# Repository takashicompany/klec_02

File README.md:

# KLEC-02 "Gravity-36"

https://x.com/Hottyhottea/status/1843859533871058982

# 部品リスト

|画像|部品名|個数|備考|
|:--|:--|:--|:--|
||KLEC-02 PCB|1||
||[Pro Micro](https://shop.yushakobo.jp/products/21)|2|どれを買っていいか分からない場合は[コンスルー付きのセット](https://shop.yushakobo.jp/products/21)の購入を推奨します。|
||[タクトスイッチ](https://shop.yushakobo.jp/products/a0800ts-01-1)|2||
||[コンスルー](https://shop.yushakobo.jp/products/31)|4|PCBとPro Microを接続する端子です。Pro Microに付属するピンヘッダでの取り付けも可能ですが、作業ミスや故障した際の取り替えが容易になりますので、**コンスルーの使用を強く推奨します。ピンヘッダでの取り付けは当キーボードと当ビルドガイドではサポートしません。** コンスルーの必要な高さはPro Microによって異なりますので、販売元にご確認ください。コンスルーについての詳細な説明は[こちら](https://scrapbox.io/self-made-kbds-ja/%E3%82%B3%E3%83%B3%E3%82%B9%E3%83%AB%E3%83%BC)をご一読ください。併せて[取り付け方の説明](https://yushakobo.zendesk.com/hc/ja/articles/360044233974-%E3%82%B3%E3%83%B3%E3%82%B9%E3%83%AB%E3%83%BC-%E3%82%B9%E3%83%97%E3%83%AA%E3%83%B3%E3%82%B0%E3%83%94%E3%83%B3%E3%83%98%E3%83%83%E3%83%80-%E3%81%AE%E5%8F%96%E3%82%8A%E4%BB%98%E3%81%91%E6%96%B9%E3%82%92%E6%95%99%E3%81%88%E3%81%A6%E4%B8%8B%E3%81%95%E3%81%84)も目を通しておくと作業がスムーズに進められます。|
||[スイッチソケット MX用](https://shop.yushakobo.jp/products/a01ps)|36|使用せずとも、PCBとキースイッチをハンダ付けすることで取り付けは可能ですが、メンテナンス性と組み立て手順を間違えた際のリカバリーを考慮すると、スイッチソケットを使用することを推奨します。|
||[MX互換キースイッチ](https://shop.yushakobo.jp/collections/all-switches)|36||
||[MX互換キーキャップ](https://shop.yushakobo.jp/collections/keycaps)|36|[こちら](https://www.keyboard-layout-editor.com/#/gists/d532e57cda0be36ffc0e33e7f8f69d8d)から各キーのサイズを確認できます。|
||[ウレタンクッション](https://shop.yushakobo.jp/products/a0800ur-01-6)|12|数はお好みで増減させてください。|
||アクリルケース|1|[こちらのデータ](https://github.com/takashicompany/klec_02/blob/master/case/klec_02_a4_yushakobo.ai)を遊舎工房の[レーザー加工サービス](https://shop.yushakobo.jp/products/lasercut?variant=48787700744423)にてカット依頼するなどして製造してください。後日に[キーボードアクリルプレート](https://shop.yushakobo.jp/products/keyboard_acrylic_plate)に追加予定です。|
||[M2スペーサー](https://shop.yushakobo.jp/products/a0800c2?variant=37665435222177)|12|長さはお好みで調整してください。Pro Microなどにもよりますが、7mm~10mmぐらいがオススメです。|
||[M2ネジ 5mm](https://shop.yushakobo.jp/products/a0800n2?variant=37665432993953)|24||

# ファームウェア
QMK Firmwareへの[プルリクエストはこちら](https://github.com/qmk/qmk_firmware/pull/24559)です。

VIAに対応したファームウェアは[こちら](https://github.com/takashicompany/klec_02/blob/master/via/takashicompany_klec_02_via.hex)です。ソースコードは[こちら](https://github.com/takashicompany/qmk_firmware/tree/master/keyboards/takashicompany/klec_02/keymaps/via)になります。

[RemapからWebブラウザを用いたファームウェアの書き込み](https://remap-keys.app/keyboards/jiZA8wP7nL4qwY1EUZ8j)とキーマップの変更が可能です。

~2024年11月5日現在、Remapの審査中ですのでRemapでキーマップを変更したい場合は[こちらのjsonファイル](https://github.com/takashicompany/klec_02/blob/master/via/via.json)をアップロードしてご利用ください。~

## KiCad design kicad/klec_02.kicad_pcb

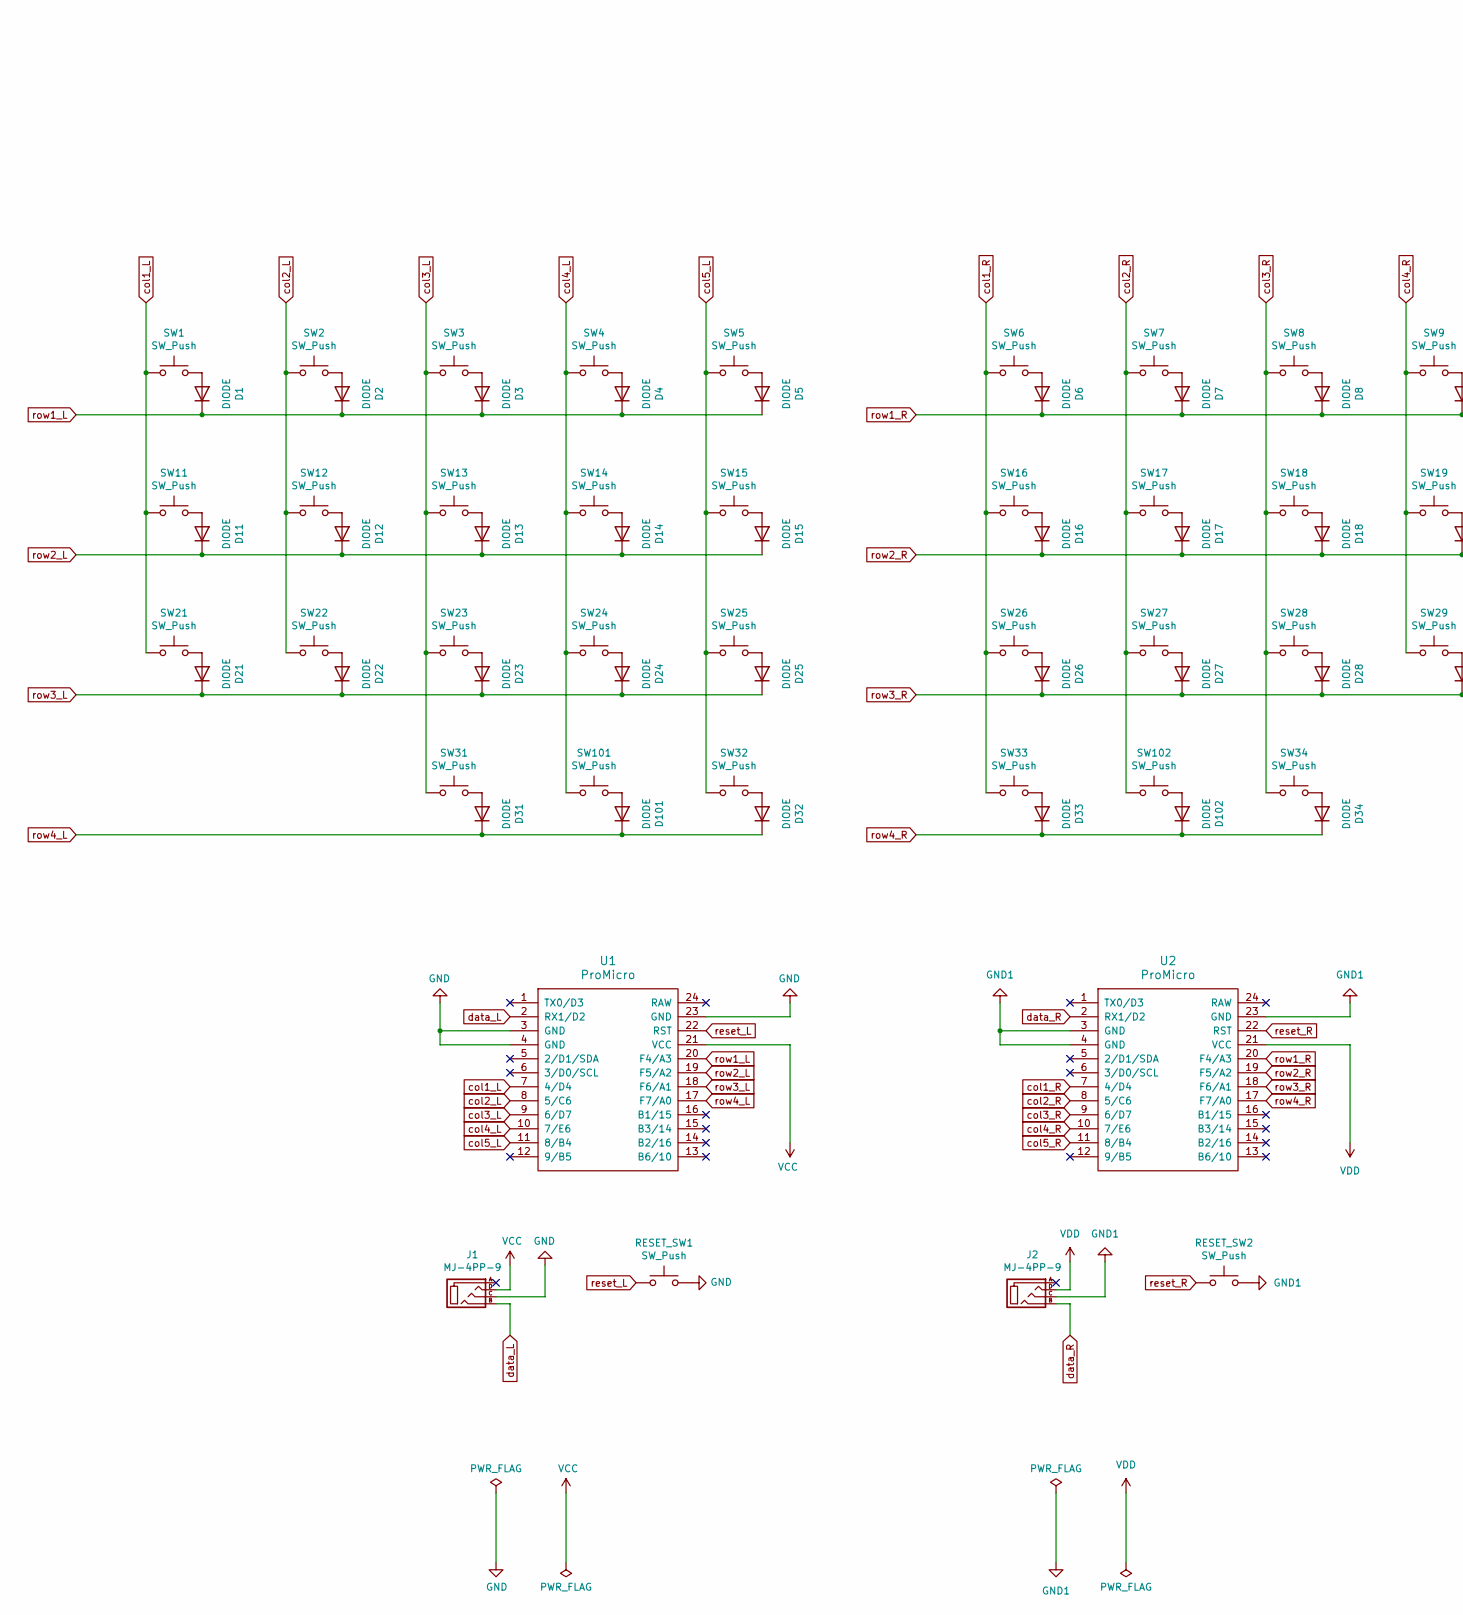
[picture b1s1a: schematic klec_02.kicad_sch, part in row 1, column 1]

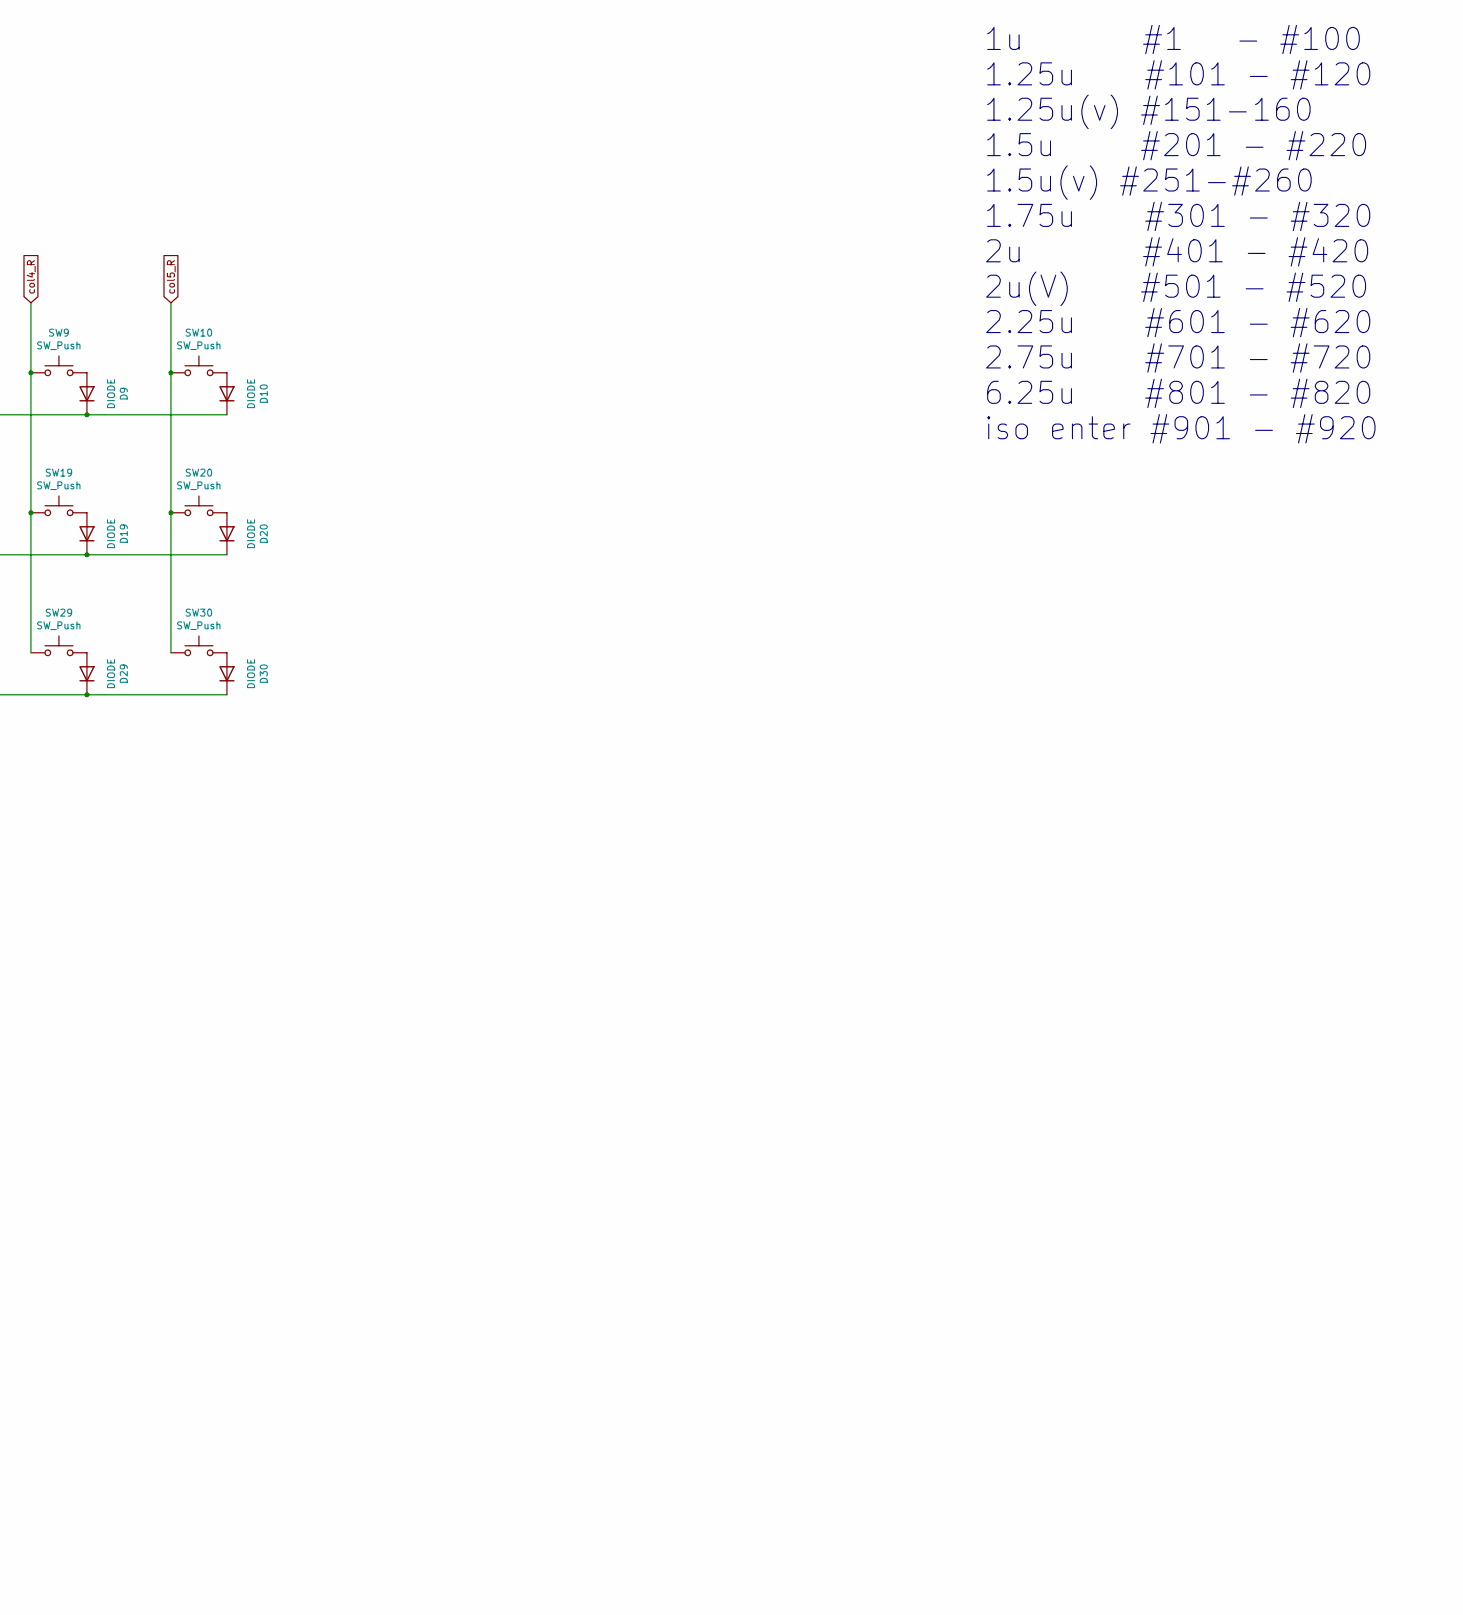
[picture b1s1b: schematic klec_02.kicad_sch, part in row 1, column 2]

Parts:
D1, D2, D3, D4, D5, D6, D7, D8, D9, D10, D11, D12, D13, D14, D15, D16, D17, D18, D19, D20, D21, D22, D23, D24, D25, D26, D27, D28, D29, D30, D31, D32, D33, D34, D101, D102: DIODE; D3_TH_SMD_v2
J1, J2: MJ-4PP-9; MJ-4PP-9_1side
RESET_SW1, RESET_SW2: SW_Push; ResetSW_1side
SW1, SW2, SW3, SW4, SW5, SW6, SW7, SW8, SW9, SW10, SW11, SW12, SW13, SW14, SW15, SW16, SW17, SW18, SW19, SW20, SW21, SW22, SW23, SW24, SW25, SW26, SW27, SW28, SW29, SW30, SW31, SW32, SW33, SW34: SW_Push; CherryMX_TH-Hotswap
SW101, SW102: SW_Push; CherryMX_TH-Hotswap_1.25u
U1, U2: ProMicro; ProMicro_v3.5_print-inside_back

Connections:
GND: J1.C, RESET_SW1.2, U1.3 (GND), U1.4 (GND), U1.23 (GND)
GND1: J2.C, RESET_SW2.2, U2.3 (GND), U2.4 (GND), U2.23 (GND)
unnamed: D1.2 (A), SW1.2
unnamed: D2.2 (A), SW2.2
unnamed: D3.2 (A), SW3.2
unnamed: D4.2 (A), SW4.2
unnamed: D5.2 (A), SW5.2
unnamed: D6.2 (A), SW6.2
unnamed: D7.2 (A), SW7.2
unnamed: D8.2 (A), SW8.2
unnamed: D9.2 (A), SW9.2
unnamed: D10.2 (A), SW10.2
unnamed: D11.2 (A), SW11.2
unnamed: D12.2 (A), SW12.2
unnamed: D13.2 (A), SW13.2
unnamed: D14.2 (A), SW14.2
unnamed: D15.2 (A), SW15.2
unnamed: D16.2 (A), SW16.2
unnamed: D17.2 (A), SW17.2
unnamed: D18.2 (A), SW18.2
unnamed: D19.2 (A), SW19.2
unnamed: D20.2 (A), SW20.2
unnamed: D21.2 (A), SW21.2
unnamed: D22.2 (A), SW22.2
unnamed: D23.2 (A), SW23.2
unnamed: D24.2 (A), SW24.2
unnamed: D25.2 (A), SW25.2
unnamed: D26.2 (A), SW26.2
unnamed: D27.2 (A), SW27.2
unnamed: D28.2 (A), SW28.2
unnamed: D29.2 (A), SW29.2
unnamed: D30.2 (A), SW30.2
unnamed: D31.2 (A), SW31.2
unnamed: D32.2 (A), SW32.2
unnamed: D33.2 (A), SW33.2
unnamed: D34.2 (A), SW34.2
unnamed: D101.2 (A), SW101.2
unnamed: D102.2 (A), SW102.2
VCC: J1.D, U1.21 (VCC)
VDD: J2.D, U2.21 (VCC)
col1_L: SW1.1, SW11.1, SW21.1, U1.7 (4/D4)
col1_R: SW6.1, SW16.1, SW26.1, SW33.1, U2.7 (4/D4)
col2_L: SW2.1, SW12.1, SW22.1, U1.8 (5/C6)
col2_R: SW7.1, SW17.1, SW27.1, SW102.1, U2.8 (5/C6)
col3_L: SW3.1, SW13.1, SW23.1, SW31.1, U1.9 (6/D7)
col3_R: SW8.1, SW18.1, SW28.1, SW34.1, U2.9 (6/D7)
col4_L: SW4.1, SW14.1, SW24.1, SW101.1, U1.10 (7/E6)
col4_R: SW9.1, SW19.1, SW29.1, U2.10 (7/E6)
col5_L: SW5.1, SW15.1, SW25.1, SW32.1, U1.11 (8/B4)
col5_R: SW10.1, SW20.1, SW30.1, U2.11 (8/B4)
data_L: J1.B, U1.2 (RX1/D2)
data_R: J2.B, U2.2 (RX1/D2)
reset_L: RESET_SW1.1, U1.22 (RST)
reset_R: RESET_SW2.1, U2.22 (RST)
row1_L: D1.1 (K), D2.1 (K), D3.1 (K), D4.1 (K), D5.1 (K), U1.20 (F4/A3)
row1_R: D6.1 (K), D7.1 (K), D8.1 (K), D9.1 (K), D10.1 (K), U2.20 (F4/A3)
row2_L: D11.1 (K), D12.1 (K), D13.1 (K), D14.1 (K), D15.1 (K), U1.19 (F5/A2)
row2_R: D16.1 (K), D17.1 (K), D18.1 (K), D19.1 (K), D20.1 (K), U2.19 (F5/A2)
row3_L: D21.1 (K), D22.1 (K), D23.1 (K), D24.1 (K), D25.1 (K), U1.18 (F6/A1)
row3_R: D26.1 (K), D27.1 (K), D28.1 (K), D29.1 (K), D30.1 (K), U2.18 (F6/A1)
row4_L: D31.1 (K), D32.1 (K), D101.1 (K), U1.17 (F7/A0)
row4_R: D33.1 (K), D34.1 (K), D102.1 (K), U2.17 (F7/A0)

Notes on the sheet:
1u #1 - #100 1.25u #101 - #120 1.25u(v) #151-160 1.5u #201 - #220 1.5u(v) #251-#260 1.75u #301 - #320 2u #401 - #420 2u(V) #501 - #520 2.25u #601 - #620 2.75u #701 - #720 6.25u #801 - #820 iso enter #901 - #920

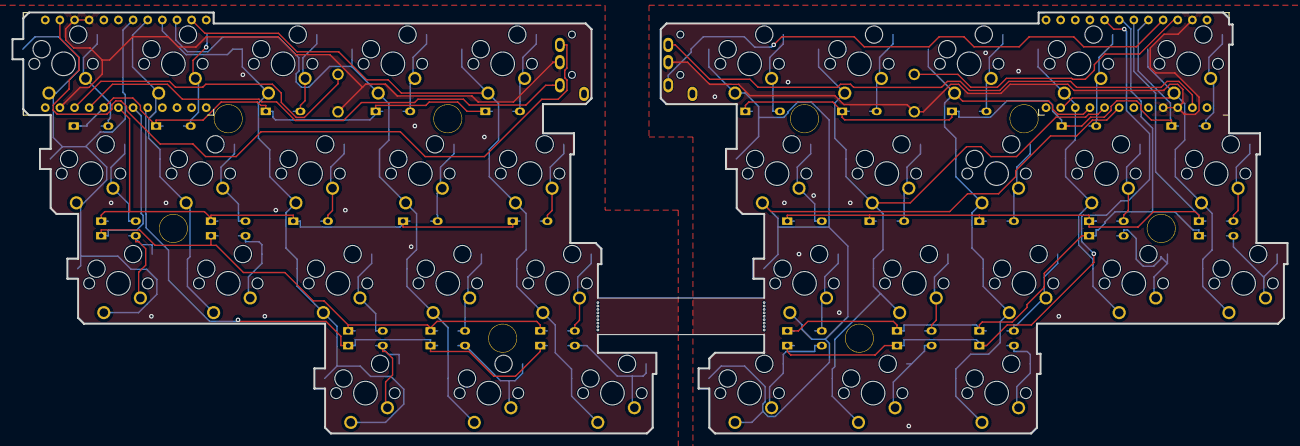
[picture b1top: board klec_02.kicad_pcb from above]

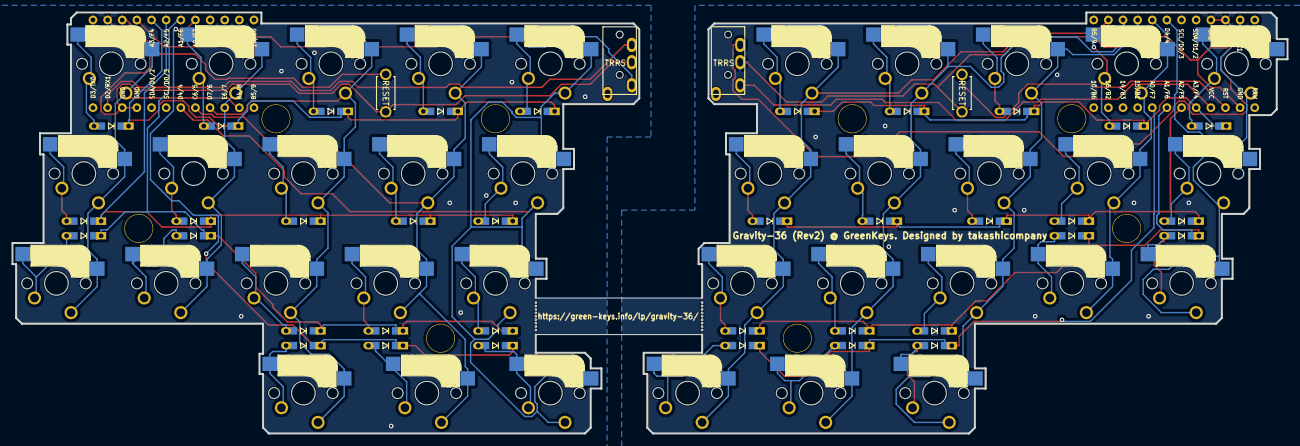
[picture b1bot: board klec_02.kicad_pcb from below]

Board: 2 copper layers, 221.3 x 73.0 mm, 88 parts (40 on the bottom side), 62 nets.

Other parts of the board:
BT1, BT2: Breakaway_Tabs
Hole1, Hole2, Hole3, Hole4, Hole5, Hole6, Hole7, Hole8: Val**; HOLE

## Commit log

2024-11-05 case
2024-11-05 viaのjson
2024-11-05 via firmware
2025-02-23 svgを再アップロード
2025-04-11 add kicad
